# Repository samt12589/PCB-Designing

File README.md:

# PCB Designing
 PCB design and Layout for energy harvesting using vibrations. Circuit crated and tested using LTSpice and Pspice simulations. Designed and Tested in hardware configuration with 24 piezo actuators.

Designed in KiCad 8.0.3

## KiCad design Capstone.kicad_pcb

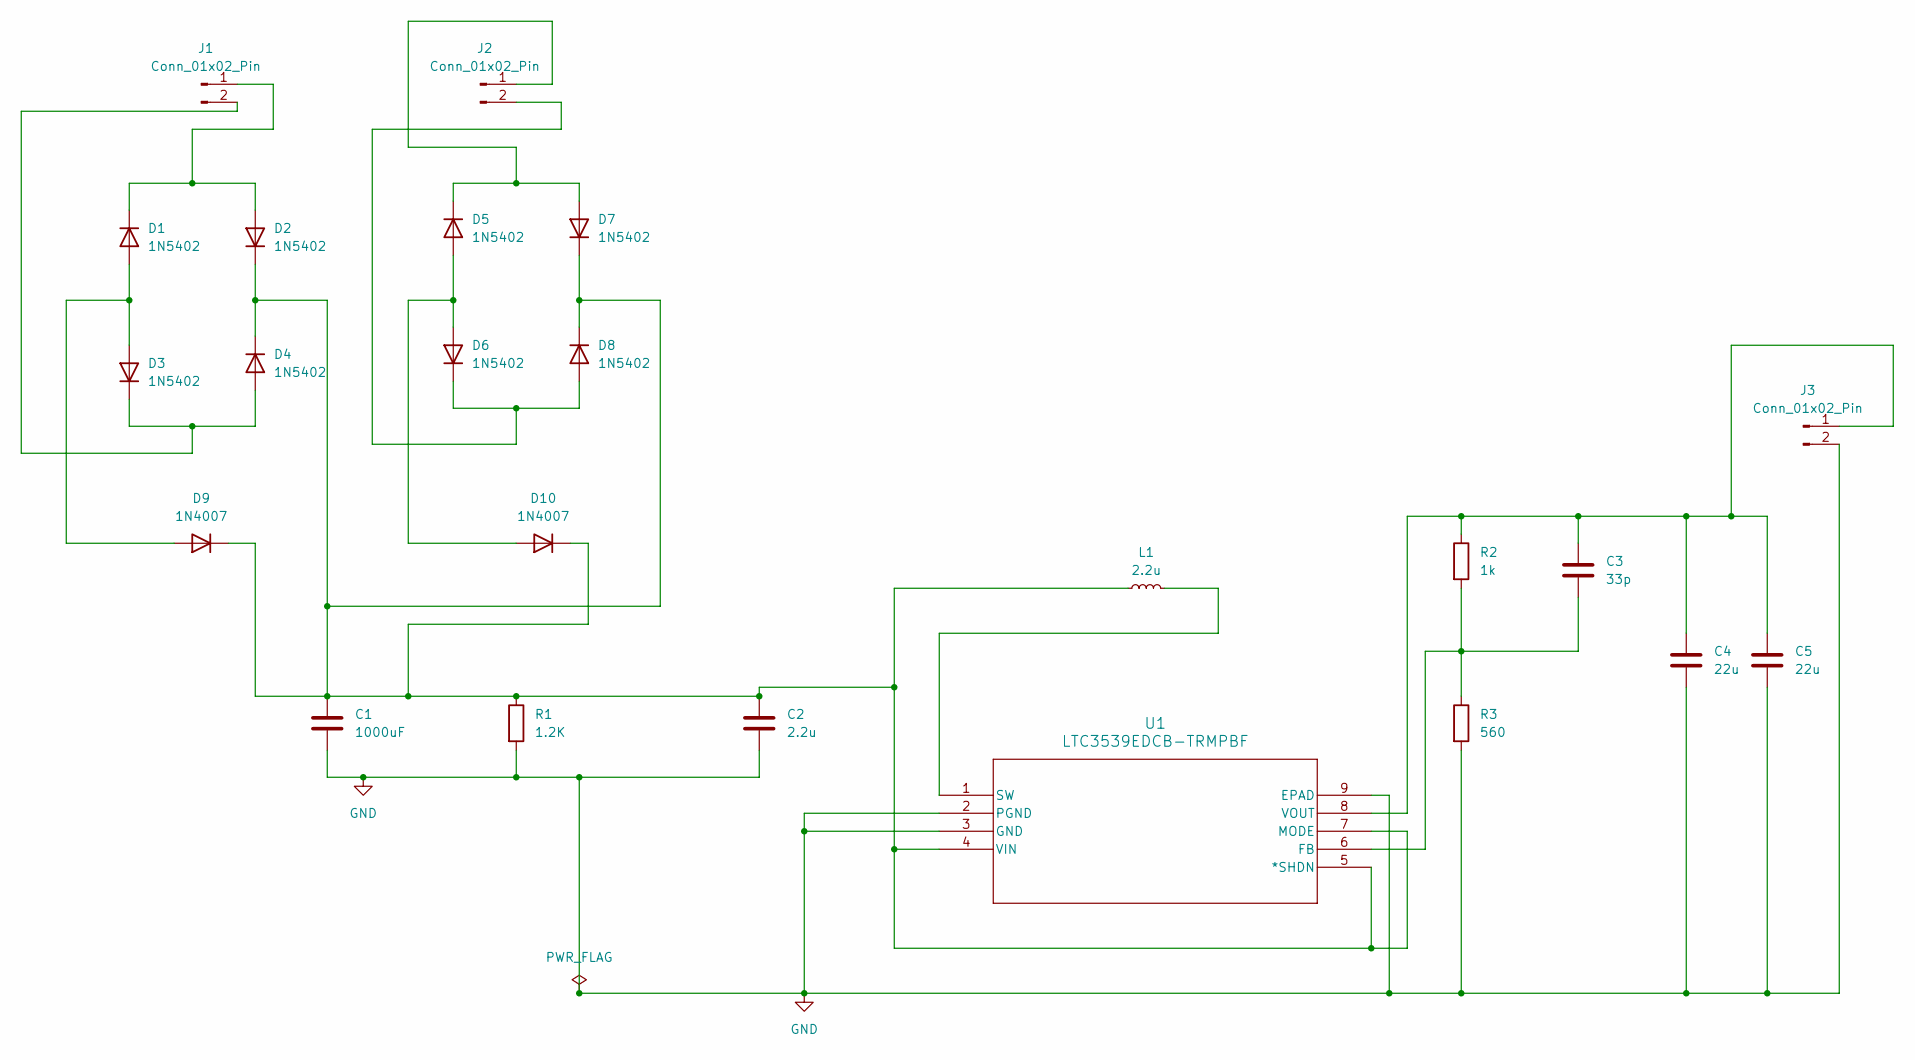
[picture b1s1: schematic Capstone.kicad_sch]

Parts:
C1: 1000uF; CP_Radial_D6.3mm_P2.50mm
C2: 2.2u; CP_Radial_D6.3mm_P2.50mm
C3: 33p; CP_Radial_D6.3mm_P2.50mm
C4, C5: 22u; CP_Radial_D6.3mm_P2.50mm
D1, D2, D3, D4, D5, D6, D7, D8: 1N5402; D_DO-34_SOD68_P7.62mm_Horizontal
D9, D10: 1N4007; D_DO-34_SOD68_P7.62mm_Horizontal
J1, J2, J3: Conn_01x02_Pin; TerminalBlock_TE_282834-2_1x02_P2.54mm_Horizontal
L1: 2.2u; L_Radial_D6.0mm_P4.00mm
R1: 1.2K; R_Axial_DIN0204_L3.6mm_D1.6mm_P5.08mm_Horizontal
R2: 1k; R_Axial_DIN0204_L3.6mm_D1.6mm_P5.08mm_Horizontal
R3: 560; R_Axial_DIN0204_L3.6mm_D1.6mm_P5.08mm_Horizontal
U1: LTC3539EDCB-TRMPBF; DFN-8_DCB_LIT-L

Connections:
GND: C1.1, C2.1, C4.1, C5.1, J3.2, R1.2, R3.2, U1.2 (PGND), U1.3 (GND), U1.9 (EPAD)
unnamed: D1.2 (A), D3.2 (A), D9.2 (A)
unnamed: D1.1 (K), D2.2 (A), J1.1
unnamed: D3.1 (K), D4.2 (A), J1.2
unnamed: D5.1 (K), D7.2 (A), J2.1
unnamed: D6.1 (K), D8.2 (A), J2.2
unnamed: D5.2 (A), D6.2 (A), D10.2 (A)
unnamed: C1.2, C2.2, D2.1 (K), D4.1 (K), D7.1 (K), D8.1 (K), D9.1 (K), D10.1 (K), L1.1, R1.1, U1.4 (VIN), U1.5 (*SHDN), U1.7 (MODE)
unnamed: C3.2, C4.2, C5.2, J3.1, R2.1, U1.8 (VOUT)
unnamed: C3.1, R2.2, R3.1, U1.6 (FB)
unnamed: L1.2, U1.1 (SW)

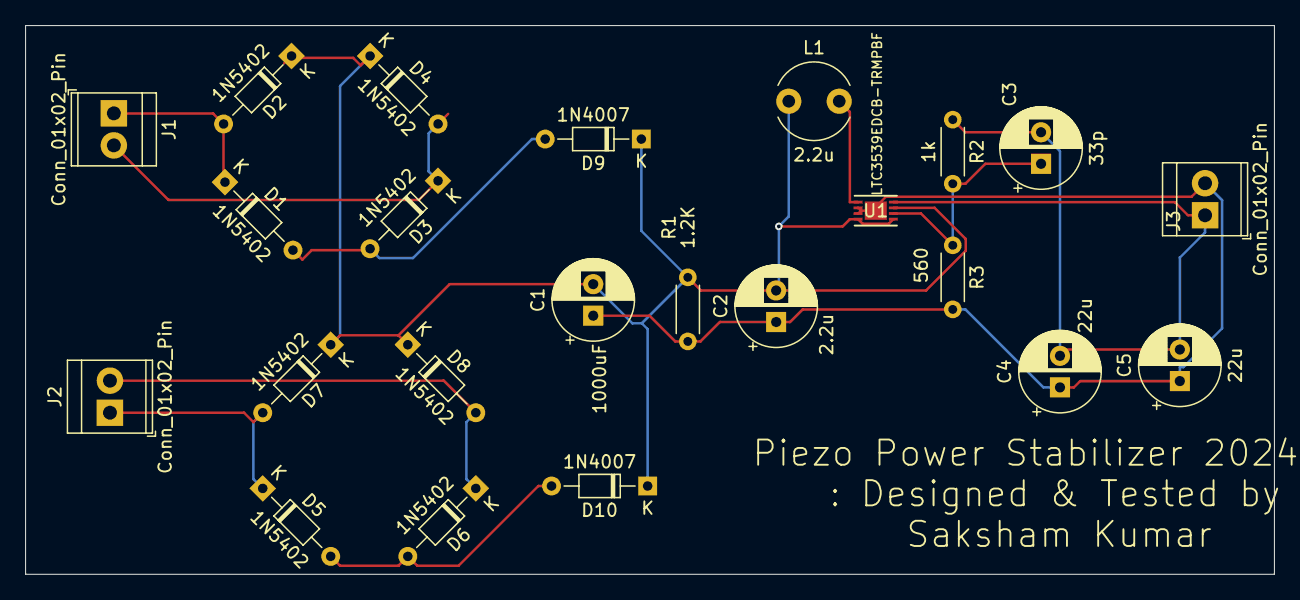
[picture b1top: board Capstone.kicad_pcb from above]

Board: 2 copper layers, 99.0 x 43.5 mm, 23 parts (0 on the bottom side), 11 nets.

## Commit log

2024-12-29 Uploading Final revision created on February 05, 2023
    Sent for printing for testing Design used with 24 piezo actuators.
